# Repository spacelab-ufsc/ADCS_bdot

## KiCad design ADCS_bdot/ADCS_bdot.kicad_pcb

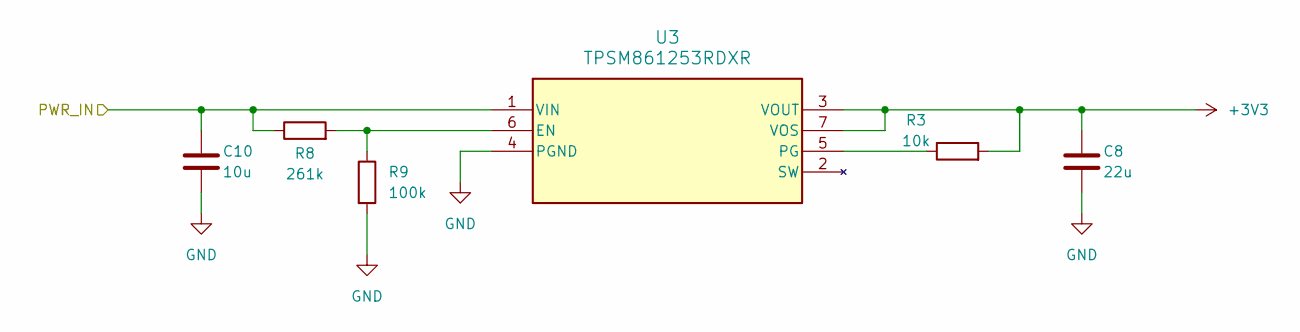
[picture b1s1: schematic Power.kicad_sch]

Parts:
C8: 22u; C_0603_1608Metric_Pad1.08x0.95mm_HandSolder
C10: 10u; C_0603_1608Metric_Pad1.08x0.95mm_HandSolder
R3: 10k; R_0603_1608Metric_Pad0.98x0.95mm_HandSolder
R8: 261k; R_0603_1608Metric_Pad0.98x0.95mm_HandSolder
R9: 100k; R_0603_1608Metric_Pad0.98x0.95mm_HandSolder
U3: TPSM861253RDXR; RDX0007A-MFG

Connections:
+3V3: C8.1, R3.2, U3.3 (VOUT), U3.7 (VOS); also elsewhere on the board
/Power/PWR_IN: C10.1, R8.1, U3.1 (VIN); also elsewhere on the board
GND: C8.2, C10.2, R9.2, U3.4 (PGND); also elsewhere on the board
unnamed 38: R8.2, R9.1, U3.6 (EN); also elsewhere on the board
unnamed: R3.1, U3.5 (PG)

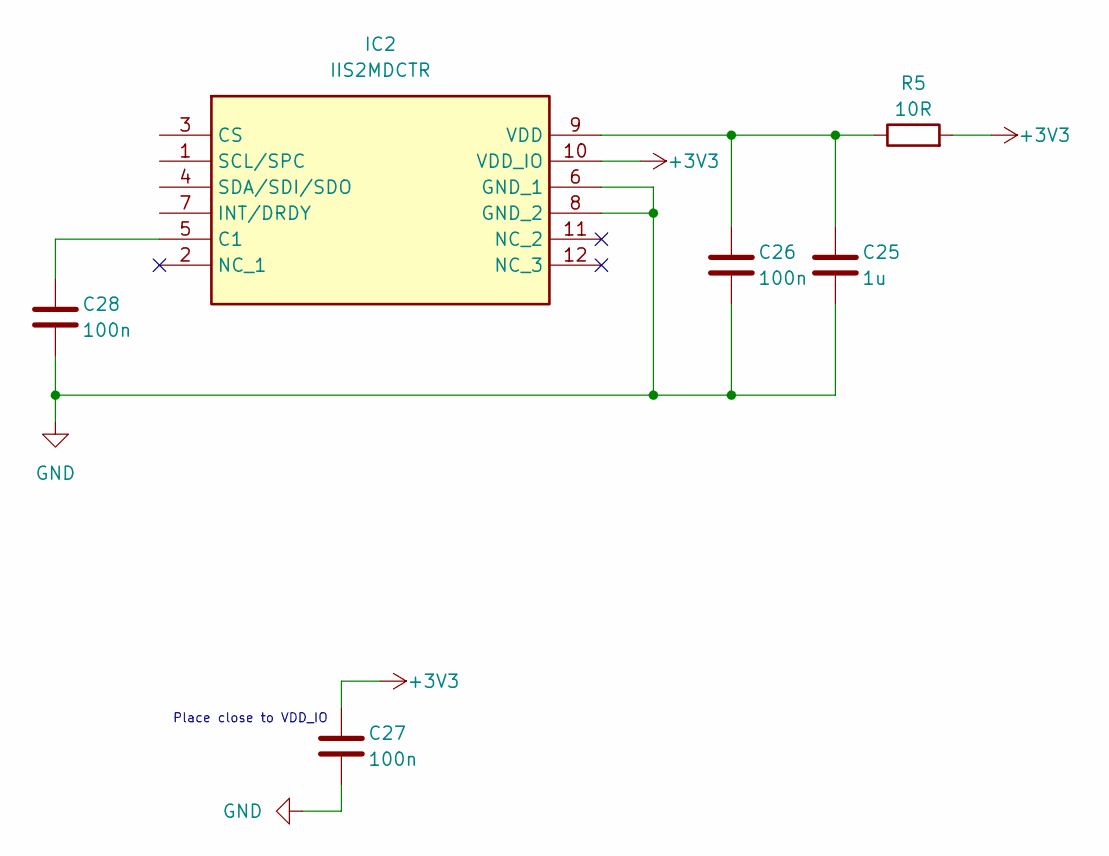
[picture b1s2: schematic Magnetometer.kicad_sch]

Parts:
C25: 1u
C26, C27, C28: 100n
IC2: IIS2MDCTR; Manufacturer_Part_Number IIS2MDCTR; Mouser Part Number 511-IIS2MDCTR
R5: 10R

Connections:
+3V3: C27.1, IC2.10 (VDD_IO), R5.2; also elsewhere on the board
/Magnetometer/CS_MAG: IC2.3 (CS)
/Magnetometer/INT_MAG: IC2.7 (INT/DRDY)
/Magnetometer/SCL: IC2.1 (SCL/SPC)
/Magnetometer/SDA: IC2.4 (SDA/SDI/SDO)
GND: C25.2, C26.2, C27.2, C28.2, IC2.6 (GND_1), IC2.8 (GND_2); also elsewhere on the board
unnamed: C28.1, IC2.5 (C1)
unnamed: C25.1, C26.1, IC2.9 (VDD), R5.1

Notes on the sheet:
Place close to VDD_IO

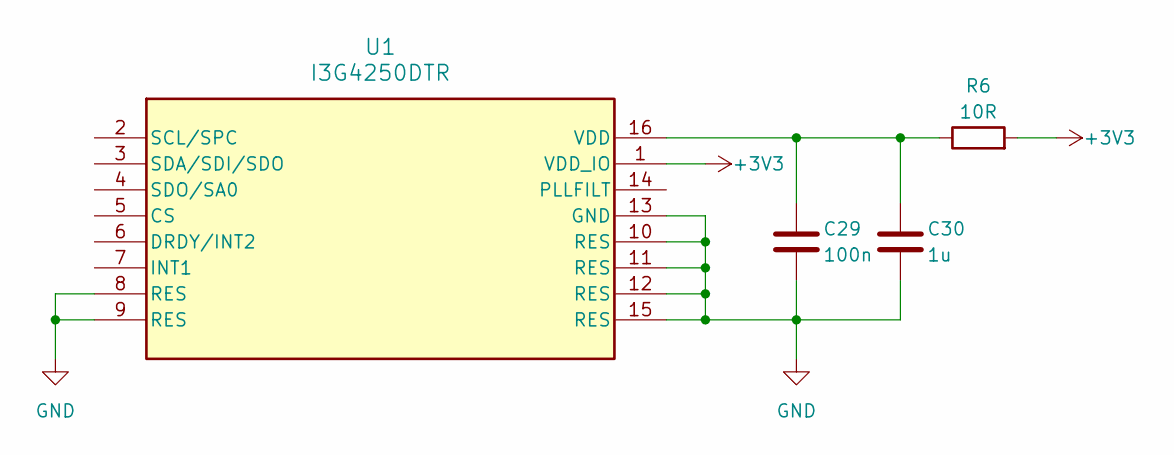
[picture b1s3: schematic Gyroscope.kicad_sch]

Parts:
C29: 100n
C30: 1u
R6: 10R
U1: I3G4250DTR; LGA-16_4X4X1_STM-M

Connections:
+3V3: R6.2, U1.1 (VDD_IO); also elsewhere on the board
/Gyroscope/CS_GYRO: U1.5 (CS)
/Gyroscope/DRDY_GYRO: U1.6 (DRDY/INT2)
/Gyroscope/INT1_GYRO: U1.7 (INT1)
/Gyroscope/SA0: U1.4 (SDO/SA0)
/Gyroscope/SCL: U1.2 (SCL/SPC)
/Gyroscope/SDA: U1.3 (SDA/SDI/SDO)
GND: C29.2, C30.2, U1.8 (RES), U1.9 (RES), U1.10 (RES), U1.11 (RES), U1.12 (RES), U1.13 (GND), U1.15 (RES); also elsewhere on the board
unnamed 36: U1.14 (PLLFILT); also elsewhere on the board
unnamed: C29.1, C30.1, R6.1, U1.16 (VDD)

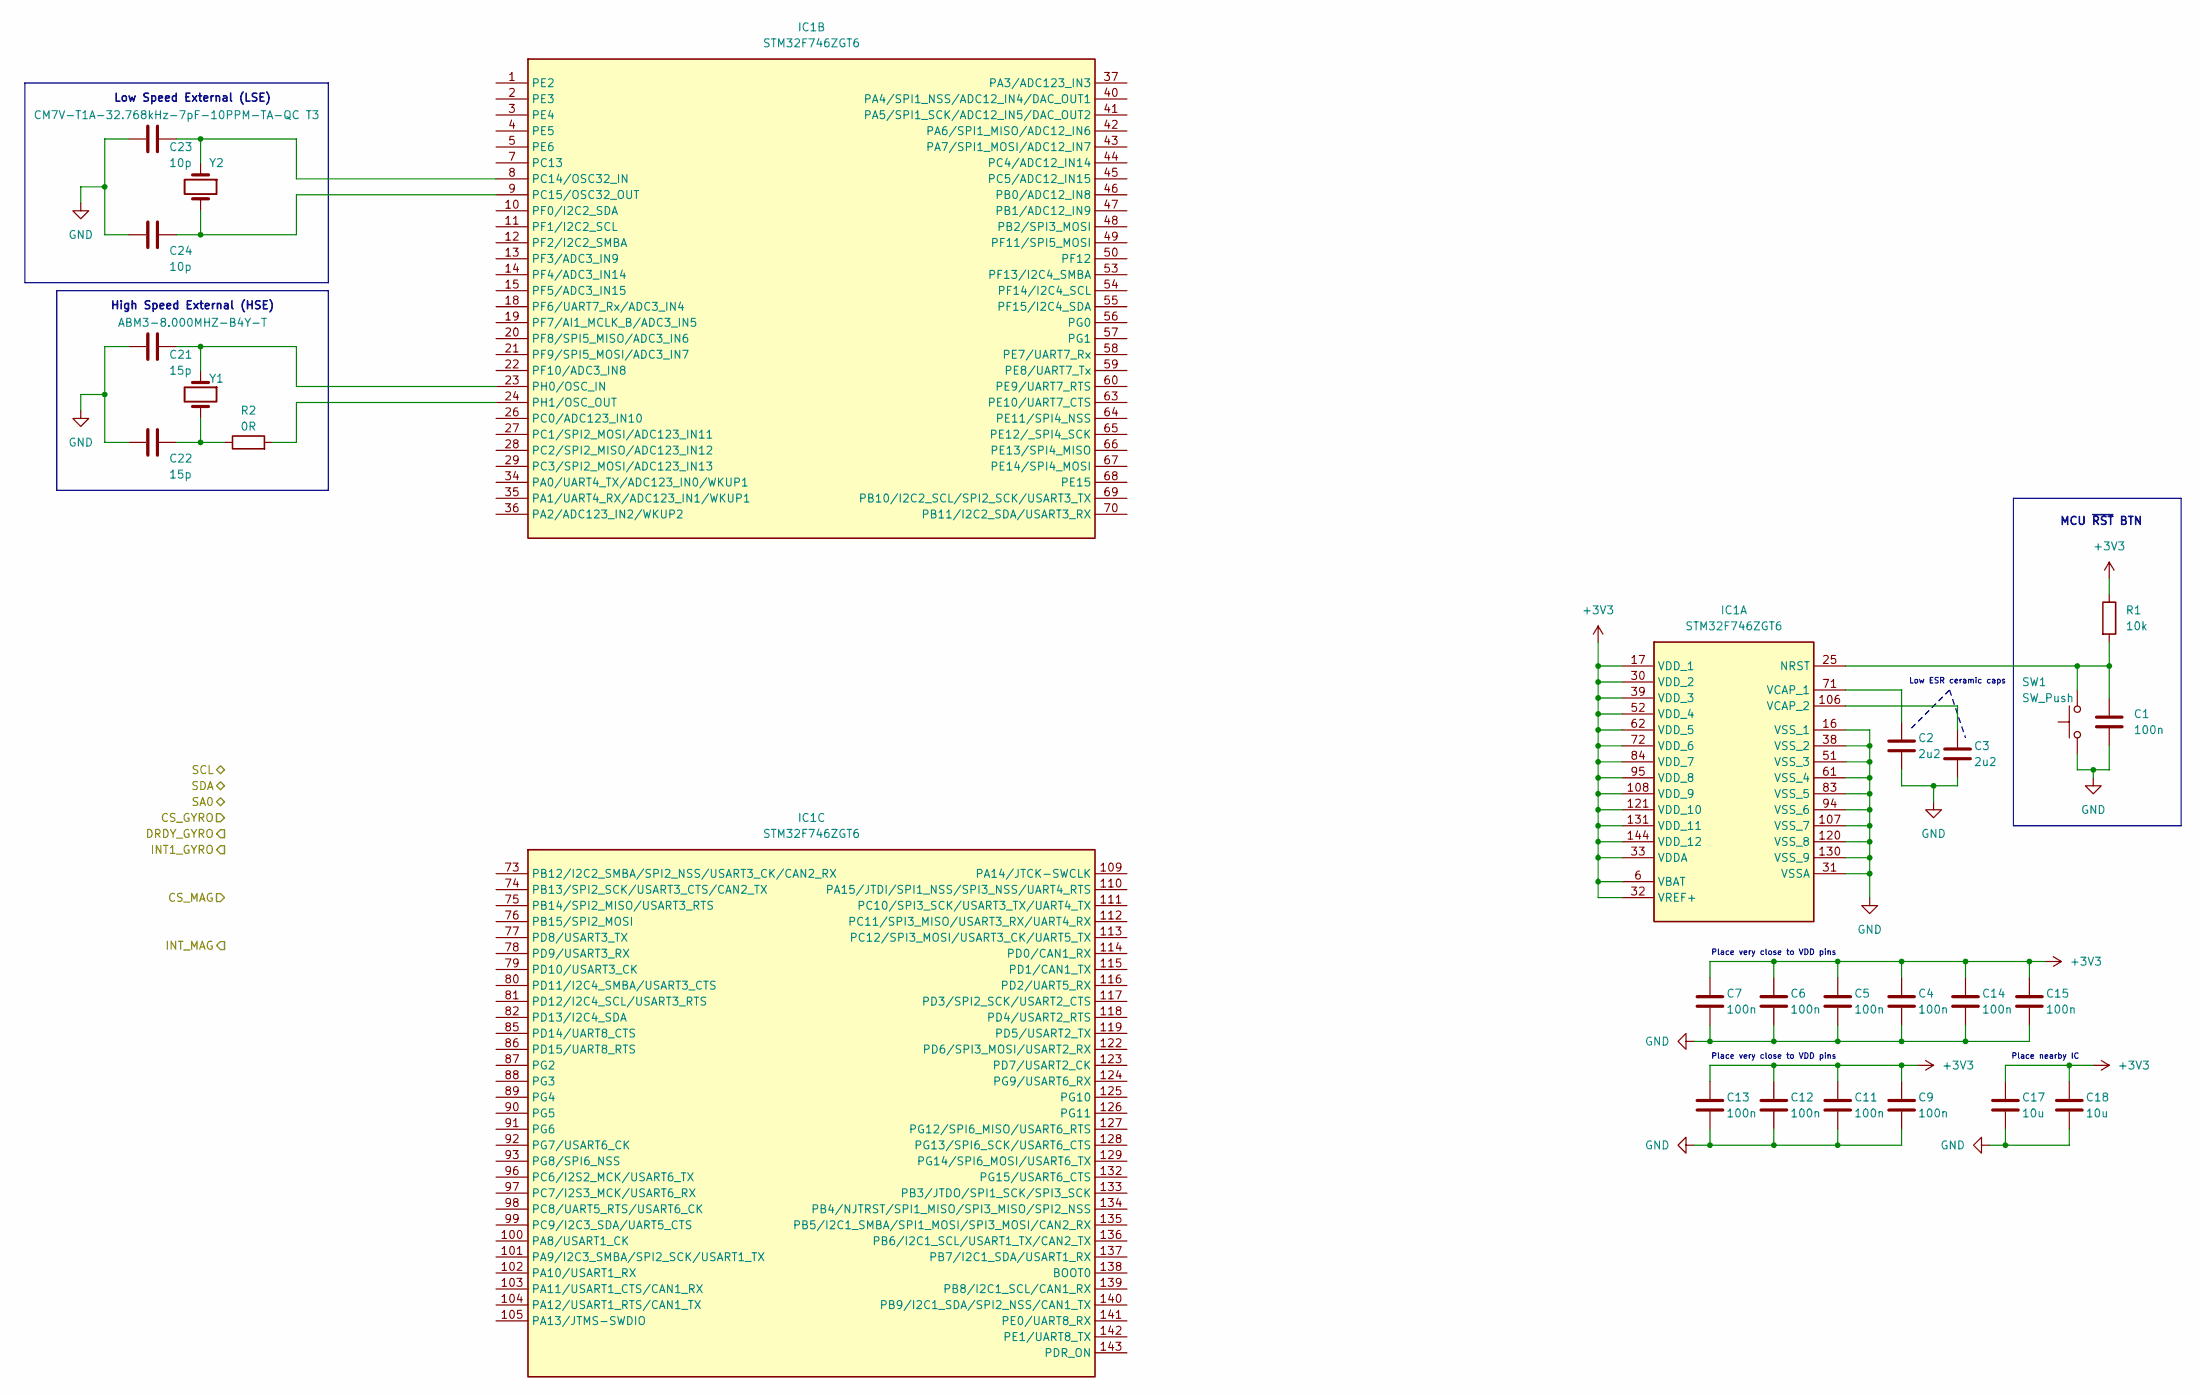
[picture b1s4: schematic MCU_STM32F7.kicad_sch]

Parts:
C1, C4, C5, C6, C7, C9, C11, C12, C13, C14, C15: 100n; C_0603_1608Metric_Pad1.08x0.95mm_HandSolder
C2, C3: 2u2; C_0603_1608Metric_Pad1.08x0.95mm_HandSolder
C17, C18: 10u; C_0603_1608Metric_Pad1.08x0.95mm_HandSolder
C21, C22: 15p; C_0603_1608Metric_Pad1.08x0.95mm_HandSolder
C23, C24: 10p; C_0603_1608Metric_Pad1.08x0.95mm_HandSolder
IC1: STM32F746ZGT6; QFP50P2200X2200X160-144N; Mouser Part Number 511-STM32F746ZGT6
R1: 10k; R_0603_1608Metric_Pad0.98x0.95mm_HandSolder
R2: 0R; R_0603_1608Metric_Pad0.98x0.95mm_HandSolder
SW1: SW_Push
Y1: ABM3-8.000MHZ-B4Y-T; ABM3
Y2: CM7V-T1A-32.768kHz-7pF-10PPM-TA-QC T3; CM7V32768TBQA020

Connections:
+3V3: C4.1, C5.1, C6.1, C7.1, C9.1, C11.1, C12.1, C13.1, C14.1, C15.1, C17.1, C18.1, IC1.6 (VBAT), IC1.17 (VDD_1), IC1.30 (VDD_2), IC1.32 (VREF+), IC1.33 (VDDA), IC1.39 (VDD_3), IC1.52 (VDD_4), IC1.62 (VDD_5), IC1.72 (VDD_6), IC1.84 (VDD_7), IC1.95 (VDD_8), IC1.108 (VDD_9), IC1.121 (VDD_10), IC1.131 (VDD_11), IC1.144 (VDD_12), R1.1; also elsewhere on the board
GND: C1.2, C2.2, C3.2, C4.2, C5.2, C6.2, C7.2, C9.2, C11.2, C12.2, C13.2, C14.2, C15.2, C17.2, C18.2, C21.2, C22.2, C23.2, C24.2, IC1.16 (VSS_1), IC1.31 (VSSA), IC1.38 (VSS_2), IC1.51 (VSS_3), IC1.61 (VSS_4), IC1.83 (VSS_5), IC1.94 (VSS_6), IC1.107 (VSS_7), IC1.120 (VSS_8), IC1.130 (VSS_9), SW1.1; also elsewhere on the board
unnamed: C22.1, R2.1, Y1.2
unnamed: C1.1, IC1.25 (NRST), R1.2, SW1.2
unnamed: C2.1, IC1.71 (VCAP_1)
unnamed: C3.1, IC1.106 (VCAP_2)
unnamed: C23.1, IC1.8 (PC14/OSC32_IN), Y2.1
unnamed: C24.1, IC1.9 (PC15/OSC32_OUT), Y2.2
unnamed: C21.1, IC1.23 (PH0/OSC_IN), Y1.1
unnamed: IC1.24 (PH1/OSC_OUT), R2.2

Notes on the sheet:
Place very close to VDD pins
Low Speed External (LSE)
MCU ~{RST} BTN
Low ESR ceramic caps
High Speed External (HSE)
Place nearby IC

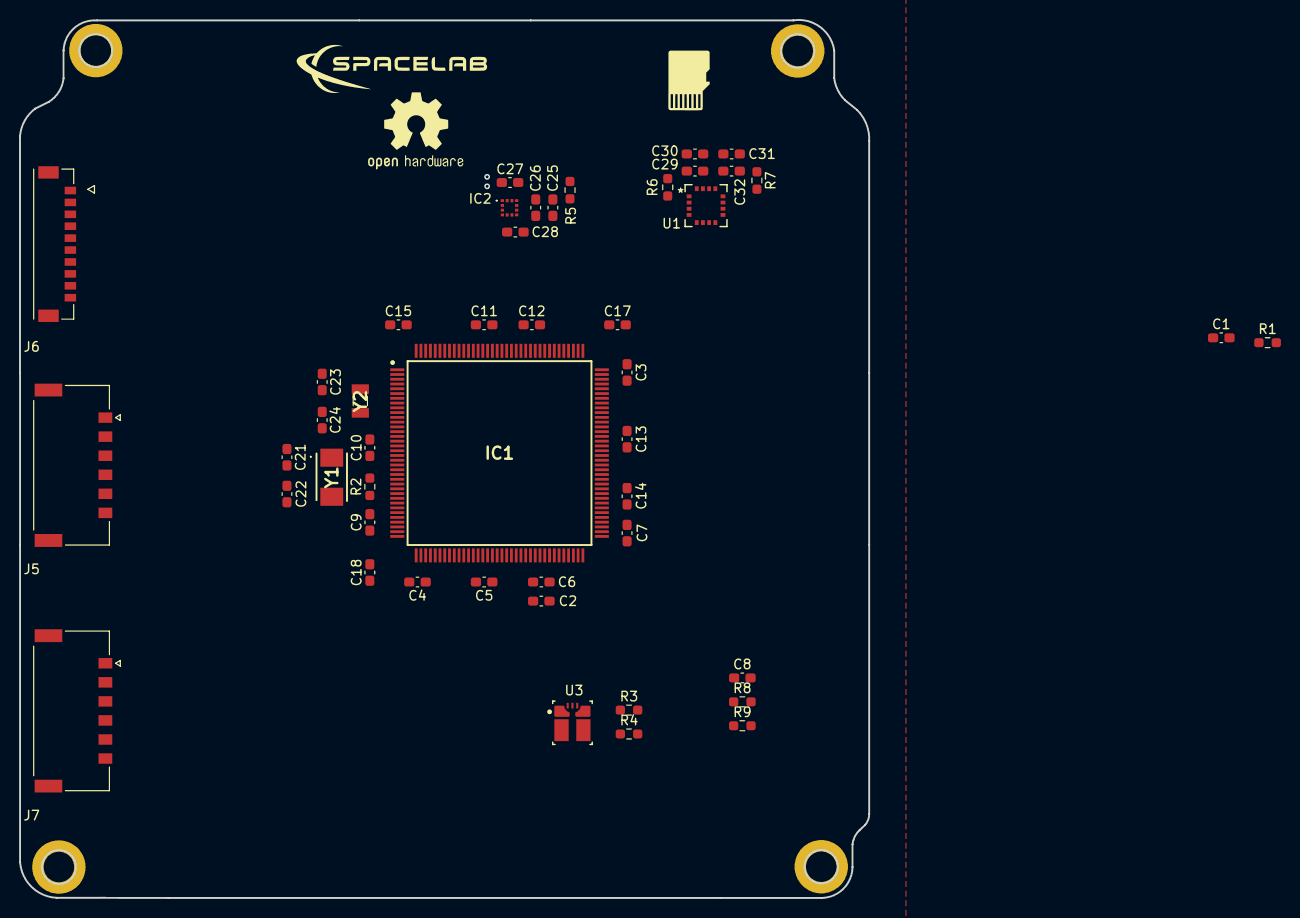
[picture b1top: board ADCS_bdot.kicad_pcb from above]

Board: 4 copper layers, 89.1 x 92.2 mm, 51 parts (0 on the bottom side), 20 nets.

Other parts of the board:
C31, C32: 100n; C_0603_1608Metric_Pad1.08x0.95mm_HandSolder
H5, H6, H7, H8: MountingHole; MountingHole_3.2mm_M3_DIN965_Pad
J5, J7: 2053380006; MOLEX_2053380006
J6: 5055671081; MOLEX_5055671081
R4: 10k; R_0603_1608Metric_Pad0.98x0.95mm_HandSolder
R7: 10R; R_0603_1608Metric_Pad0.98x0.95mm_HandSolder

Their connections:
+3V3: J5.6, J6.3; also elsewhere on the board
/Power/PWR_IN: R4.1; also elsewhere on the board
/mcu_circuits/can_n: J5.2, J6.6
/mcu_circuits/can_p: J5.1, J6.5
GND: C31.2, J5.5, J6.2, J6.8, J6.9, R7.2; also elsewhere on the board
unnamed: C32.2, R7.1
unnamed 36: C31.1, C32.1; also elsewhere on the board
unnamed 38: R4.2; also elsewhere on the board

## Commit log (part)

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2026-03-31 add: components
    MCU, MAG, GYRO
2026-03-31 add: schematic MCU Gyro Mag PWR
2026-04-01 feat: Gyro and Mag RC Filter
2026-04-12 add: a bunch of stuff
